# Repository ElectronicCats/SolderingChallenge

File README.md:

Introduction
============

## Version 2.0
New version 2.0 with Microcontroller PUYA available now!!

## Version 1
This design is based on the work of [aspro648](https://github.com/aspro648) you can support him buying his stuff at [Tindie](https://www.tindie.com/products/MakersBox/smd-challenge/)

This design was possible thanks to [Mouser electronics](https://iopscience.iop.org/journal/2041-8205/page/Focus_on_EHT), [Würth Elektronik](https://www.we-online.com/web/en/electronic_components/willkommen_pbs/Welcome.php) and [Makers GDL](https://makersgdl.com/) we really appreciate all your support to get this boards free for the Talent Land 2019.

Test your surface mount soldering skills out, starting with a 1206 package and work your way down into the humanly possible solder device, the 0402. Powered by a CR2032 coin cell and Attiny 85 SOIC. 

Design Files
============
This project is designed using Open Source [KiCad](http://kicad.org/). Design files are located in the [Hw](Hw/) folder.  You can oogle the [schematic](Images/solderingChallenge.pdf).

Firmware
========
This project is programed using the Open Source [Arduino](https://www.arduino.cc/). I use my Open Source [AVR Programming Shield](https://www.tindie.com/products/MakersBox/yet-another-programming-shield/) to program the Attiny. The firmware is located in the [firmware](Fw/) folder.

Assembly Instructions
=====================
[Aspro648](https://github.com/aspro648) have posted [minimal instructions at HackADay](https://hackaday.io/project/25265-an-unfortunate-smd-project).

License
=======
[Attribution-ShareAlike 3.0 United States (CC BY-SA 3.0 US)](https://creativecommons.org/licenses/by-sa/3.0/us/)

You are free to:

- Share — copy and redistribute the material in any medium or format
- Adapt — remix, transform, and build upon the material

Under the following terms:

- Attribution — You must give appropriate credit, provide a link to the license, and indicate if changes were made. You may do so in any reasonable manner, but not in any way that suggests the licensor endorses you or your use.
- ShareAlike — If you remix, transform, or build upon the material, you must distribute your contributions under the same license as the original.

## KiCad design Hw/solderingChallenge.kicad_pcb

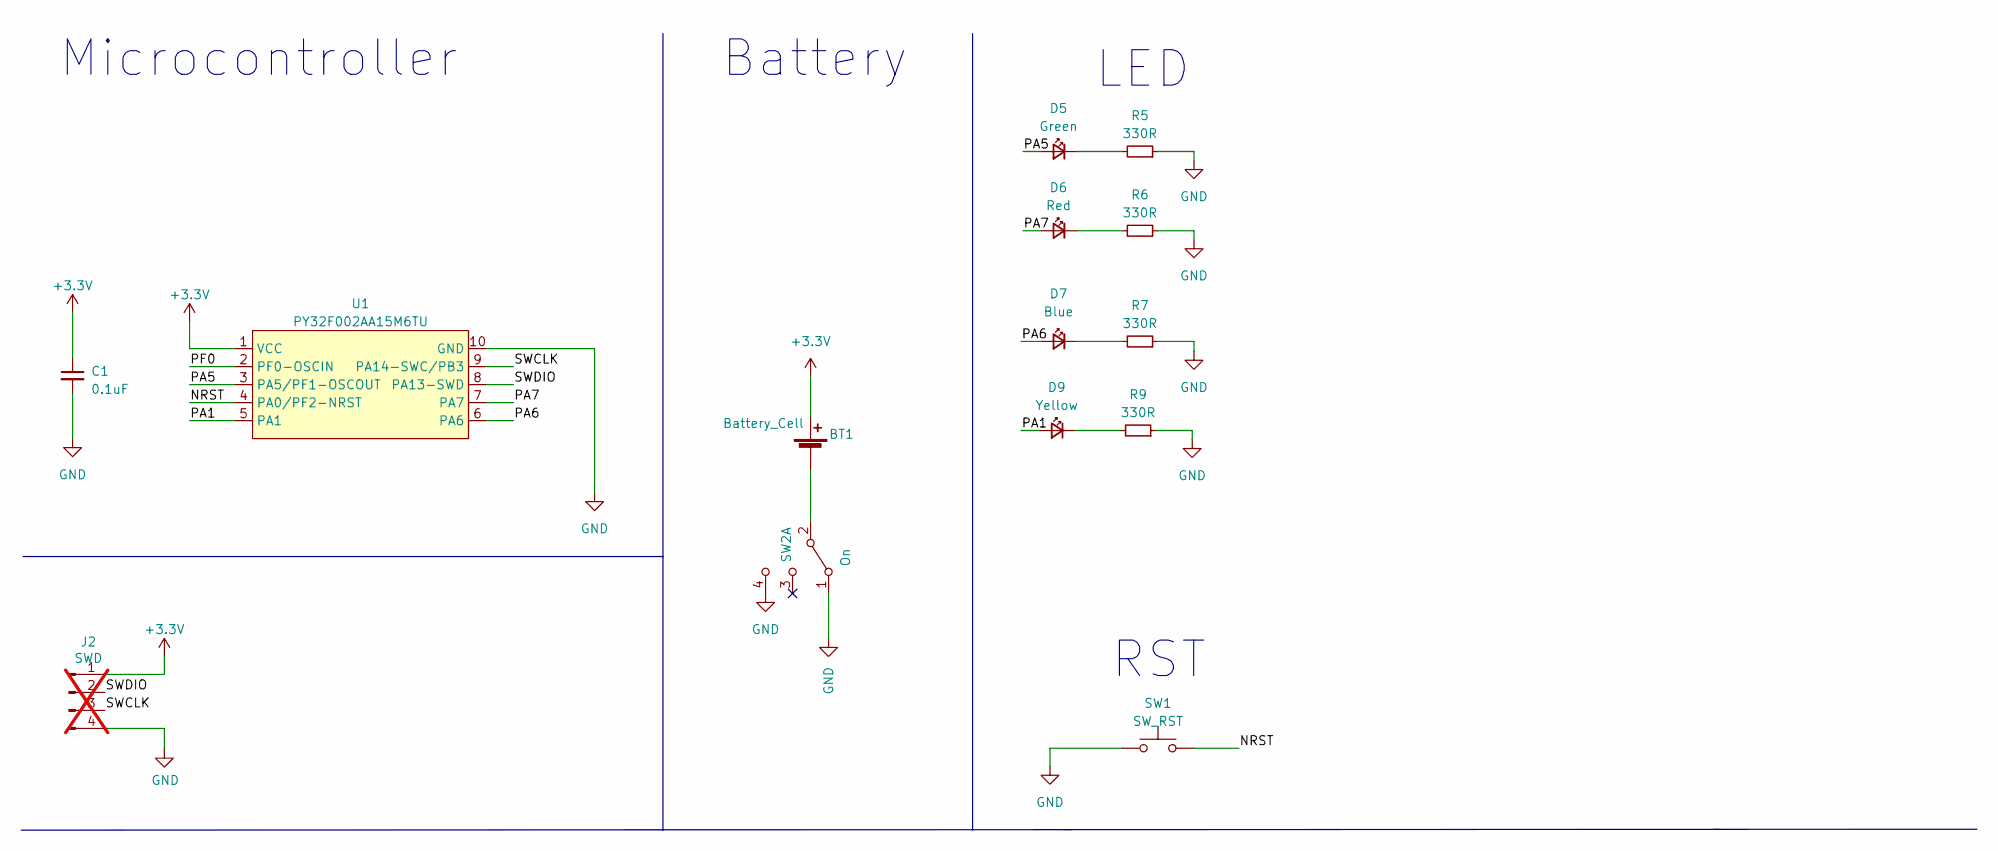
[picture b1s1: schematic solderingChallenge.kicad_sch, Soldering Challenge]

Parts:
BT1: Battery_Cell; BAT-HLD-001; LCSC# C964833
C1: 0.1uF; C_0805_2012Metric; LCSC# C38141
D5: Green; LED_1206_3216Metric_Pad1.42x1.75mm_HandSolder; LCSC# C965825
D6: Red; LED_0805_2012Metric; LCSC# C965812
D7: Blue; LED_0603_1608Metric_Pad1.05x0.95mm_HandSolder; LCSC# C965807
D9: Yellow; LED_0402_1005Metric_Pad0.77x0.64mm_HandSolder; LCSC# C434450
J2: SWD; PinHeader_1x04_P2.54mm_Vertical; not fitted
R5: 330R; R_1206_3216Metric_Pad1.30x1.75mm_HandSolder; LCSC# C2907482
R6: 330R; R_0805_2012Metric; LCSC# C119075
R7: 330R; R_0603_1608Metric_Pad0.98x0.95mm_HandSolder; LCSC# C23138
R9: 330R; R_0402_1005Metric_Pad0.72x0.64mm_HandSolder; LCSC# C25104
SW1: SW_RST; SW_SPST_TL3342; LCSC# C318889
SW2: On; MSK12C02; LCSC# C431540
U1: PY32F002AA15M6TU; PY32F002AA15M; LCSC# C5292058

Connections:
+3.3V: BT1.2 (+), C1.1, J2.1, U1.1 (VCC)
/NRST: SW1.2, U1.4 (PA0/PF2-NRST)
/PA1: D9.2 (A), U1.5 (PA1)
/PA5: D5.2 (A), U1.3 (PA5/PF1-OSCOUT)
/PA6: D7.2 (A), U1.6 (PA6)
/PA7: D6.2 (A), U1.7 (PA7)
/PF0: U1.2 (PF0-OSCIN)
/SWCLK: J2.3, U1.9 (PA14-SWC/PB3)
/SWDIO: J2.2, U1.8 (PA13-SWD)
GND: C1.2, J2.4, R5.1, R6.1, R7.1, R9.1, SW1.1, SW2.1 (A), SW2.4 (C), U1.10 (GND)
unnamed: BT1.1 (-), SW2.2 (B)
unnamed: D5.1 (K), R5.2
unnamed: D6.1 (K), R6.2
unnamed: D7.1 (K), R7.2
unnamed: D9.1 (K), R9.2

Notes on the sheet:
Microcontroller
RST
Battery
LED

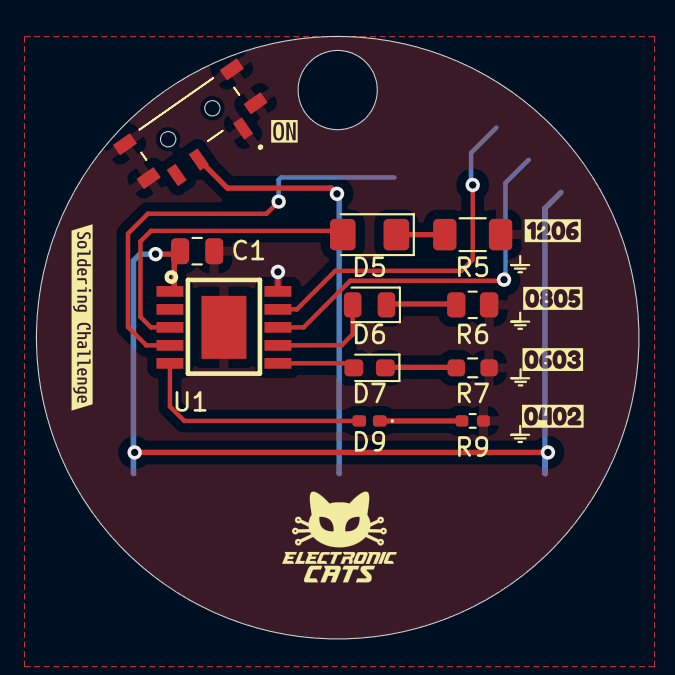
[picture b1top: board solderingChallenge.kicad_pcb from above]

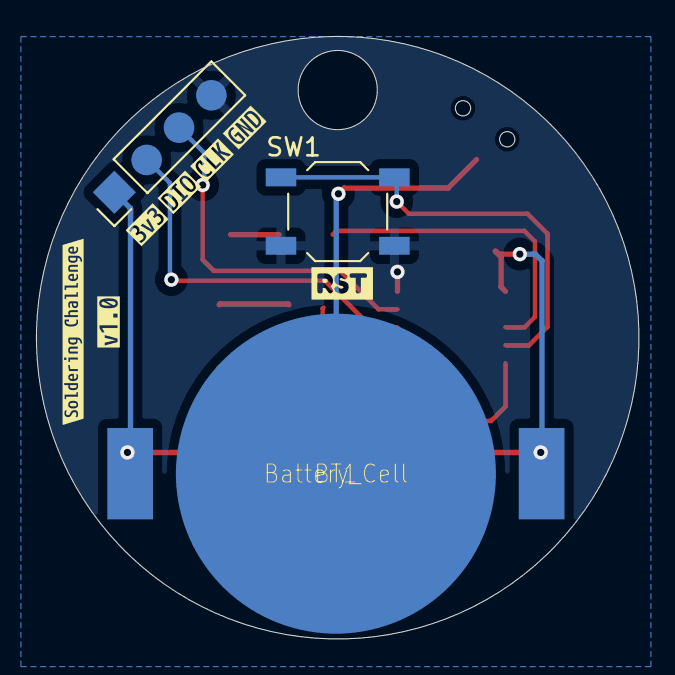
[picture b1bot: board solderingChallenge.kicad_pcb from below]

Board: 2 copper layers, 33.5 x 33.5 mm, 27 parts (10 on the bottom side), 14 nets.

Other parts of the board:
kibuzzard-6797B453: G***; kibuzzard-6797B453
kibuzzard-67914DBF: G***; kibuzzard-67914DBF
kibuzzard-67914DD8: G***; kibuzzard-67914DD8
kibuzzard-67914DE9: G***; kibuzzard-67914DE9
kibuzzard-67914E01: G***; kibuzzard-67914E01
kibuzzard-67916B62: G***; kibuzzard-67916B62
kibuzzard-679163A9: G***; kibuzzard-679163A9
kibuzzard-679163CD: G***; kibuzzard-679163CD
kibuzzard-679168C7: G***; kibuzzard-679168C7
kibuzzard-679168F3: G***; kibuzzard-679168F3
kibuzzard-67916383: G***; kibuzzard-67916383
kibuzzard-67996501, kibuzzard-67996501#2: G***; kibuzzard-67996501

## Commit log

2019-04-09 add gitignore
2019-04-09 Add kicad project
2019-04-09 Update gitignore
2019-04-09 Update connections
2019-04-09 add logo wurth
2019-04-09 Change capacitor size
2019-04-11 Update version
2019-04-11 Update logos and version
2019-04-11 V1.0
2019-04-11 Add images
2019-04-11 Add SVG of schematic
2019-04-11 Add Fw
2019-04-11 add hex
2019-04-11 Fix typo in README
2019-04-11 Create LICENSE
2021-11-09 Update README.md
    https://forum.kicad.info/t/warning-avoid-all-links-to-kicad-pcb-org-use-kicad-org/31521
2025-01-22 feat(Hw):Added_Puya_PCB
2025-01-22 feat(Hw):Update_csv
2025-01-24 feat(Hw):Align_Components
2025-01-27 feat: add labels
2025-01-29 fix(Hw): Update Logo and tags
2025-02-24 docs: Update README.md with v2.0
